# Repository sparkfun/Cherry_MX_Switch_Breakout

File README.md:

SparkFun Cherry MX Switch Breakout
====================

<table class="table table-hover table-striped table-bordered">
  <tr align="center">
   <td></td>
   <td></td>
  </tr>
  <tr align="center">
    <td><i>SparkFun Cherry MX Switch Breakout </i></td>
    <td><i>Cherry MX Switch Soldered on Breakout</i></td>
  </tr>
</table>

[*SparkFun Cherry MX Switch Breakout (BOB-13773)*](https://www.sparkfun.com/products/13773)

Cherry MX Keyswitches are top-of-the-line mechanical keyboard switches. They’re satisfyingly “clicky”, reliable up to tens-of-millions of key presses, and a standard in gaming and programming keyboards across the globe. With the SparkFun Cherry MX Switch Breakout we have made the switches more easily adaptable to breadboard or perfboard-based projects. The Cherry MX Switch Breakout is a perfect prototyping tool for projects ranging from a single-key user-input to fully-custom 101-key keyboards.

Repository Contents
-------------------

* **/Hardware** - All Eagle design files (.brd, .sch)
* **/Production** - Production panel files (.brd)

Documentation
--------------
* **[Hookup Guide](https://learn.sparkfun.com/tutorials/cherry-mx-switch-breakout-hookup-guide)** - Basic hookup guide for the SparkFun Cherry MX Switch Breakout.

Product Versions
----------------
* [BOB-13773](https://www.sparkfun.com/products/13773)- Initial release of the Cherry MX Switch Breakout

Version History
---------------
* [V_1.0](https://github.com/sparkfun/Cherry_MX_Switch-Breakout/releases/tag/V_1.0) - Initial release of Cherry MX Switch Breakout.

License Information
-------------------

This product is _**open source**_! 

Please review the LICENSE.md file for license information. 

If you have any questions or concerns on licensing, please contact techsupport@sparkfun.com.

Distributed as-is; no warranty is given.

- Your friends at SparkFun.

_<COLLABORATION CREDIT>_

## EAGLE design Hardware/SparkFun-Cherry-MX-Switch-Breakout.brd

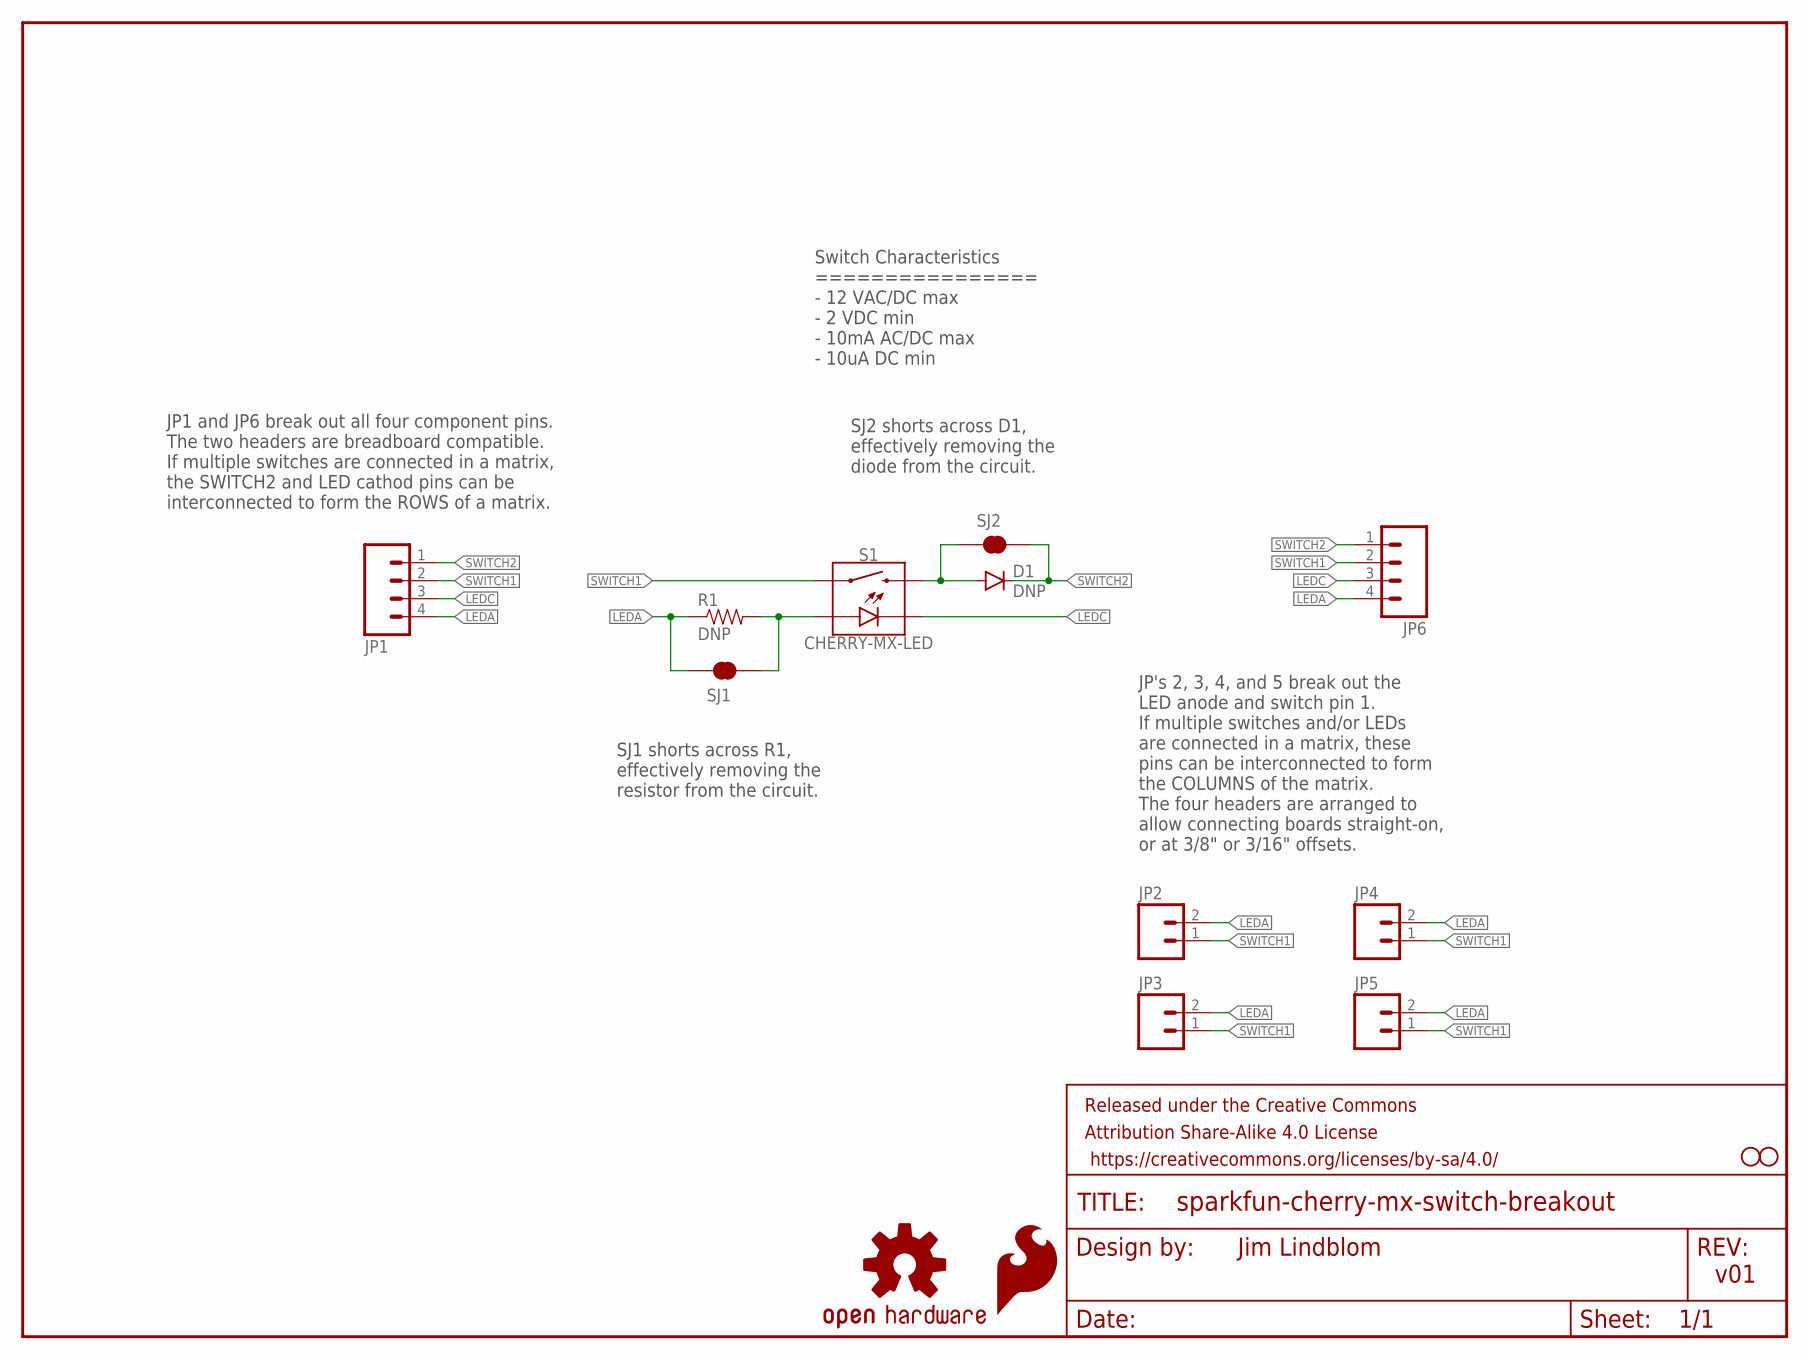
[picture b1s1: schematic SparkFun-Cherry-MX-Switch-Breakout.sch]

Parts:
D1: DNP; DIODE-PTH-0.1
FRAME1: FRAME-LETTER; CREATIVE_COMMONS
JP1, JP6: M04NO_SILK_ALL_ROUND; 1X04_NO_SILK_ALL_ROUND
JP2, JP3, JP4, JP5: M021X02_NO_SILK; 1X02_NO_SILK
LOGO1: OSHW-LOGOS; OSHW-LOGO-S
LOGO2: SFE_LOGO_FLAME.1_INCH; SFE_LOGO_FLAME_.1
R1: DNP; AXIAL-0.1
S1: CHERRY-MX-LED
SJ1, SJ2: JUMPER-PAD-2-NC_BY_TRACENO_SILK; PAD-JUMPER-2-NC_BY_TRACE_NO_SILK
STANDOFF1, STANDOFF2: STAND-OFF2-56; STAND-OFF-2-56

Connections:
LEDA: JP1.4, JP2.2, JP3.2, JP4.2, JP5.2, JP6.4, R1.P$1 (1), SJ1.1
LEDC: JP1.3, JP6.3, S1.K (C)
unnamed: R1.P$2 (2), S1.A, SJ1.2
unnamed: D1.A, S1.S2, SJ2.1
SWITCH1: JP1.2, JP2.1, JP3.1, JP4.1, JP5.1, JP6.2, S1.S1
SWITCH2: D1.C, JP1.1, JP6.1, SJ2.2

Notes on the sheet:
v01
Jim Lindblom
SJ1 shorts across R1, effectively removing the resistor from the circuit.
SJ2 shorts across D1, effectively removing the diode from the circuit.
JP's 2, 3, 4, and 5 break out the LED anode and switch pin 1. If multiple switches and/or LEDs are connected in a matrix, these pins can be interconnected to form the COLUMNS of the matrix. The four headers are arranged to allow connecting boards straight-on, or at 3/8" or 3/16" offsets.
JP1 and JP6 break out all four component pins. The two headers are breadboard compatible. If multiple switches are connected in a matrix, the SWITCH2 and LED cathod pins can be interconnected to form the ROWS of a matrix.
Switch Characteristics ================ - 12 VAC/DC max - 2 VDC min - 10mA AC/DC max - 10uA DC min

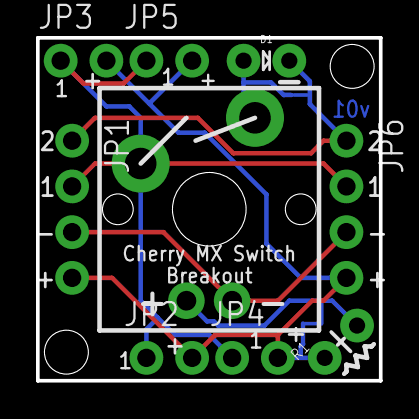
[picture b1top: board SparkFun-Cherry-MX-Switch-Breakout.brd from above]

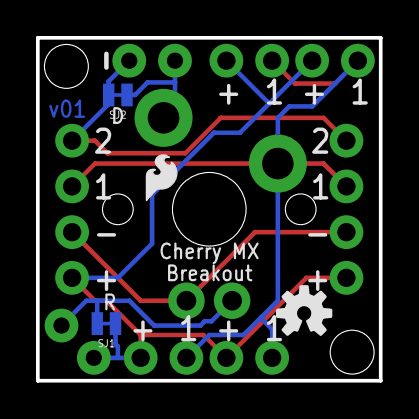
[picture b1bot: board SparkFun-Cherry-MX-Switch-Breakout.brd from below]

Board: 2 copper layers, 19.1 x 19.1 mm, 16 parts (4 on the bottom side), 6 nets.

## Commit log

2015-11-23 Initial commit of board design
2015-11-23 Rearranging resistor and diode packages and standoffs.
2015-11-23 Polishing resistor and diode silk.
2015-11-23 Removing extra 2-pin connector.
2015-12-22 Adjsting some silk, setting version to v10.

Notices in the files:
parts and their libraries:
SparkFun-Aesthetics: Licensing: Creative Commons ShareAlike 4.0 International - https://creativecommons.org/licenses/by-sa/4.0
SparkFun-Aesthetics: Released under the Creative Commons Attribution Share-Alike 4.0 License
SparkFun-Aesthetics: https://creativecommons.org/licenses/by-sa/4.0
